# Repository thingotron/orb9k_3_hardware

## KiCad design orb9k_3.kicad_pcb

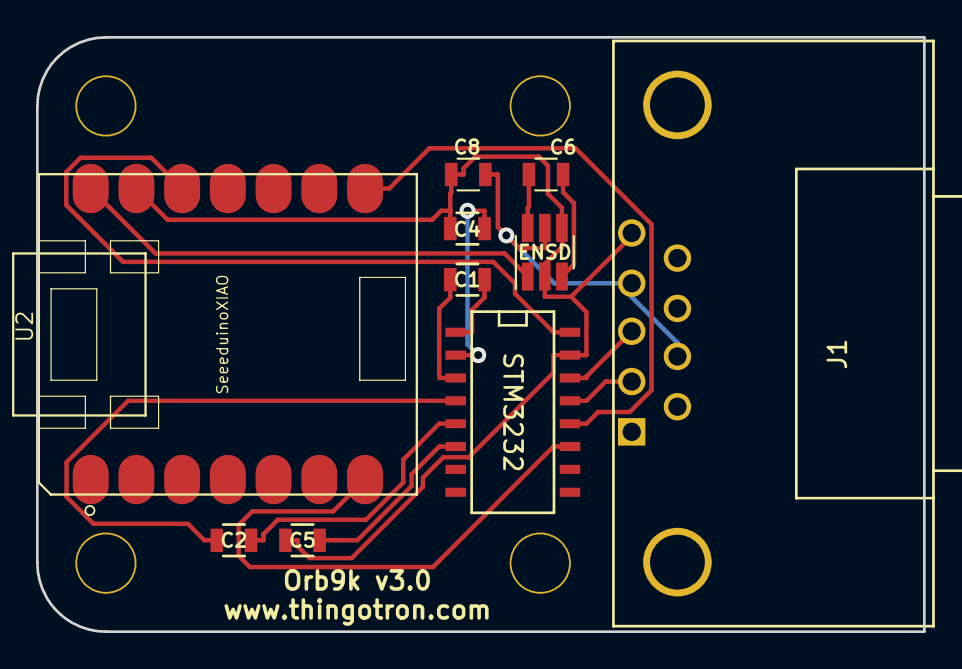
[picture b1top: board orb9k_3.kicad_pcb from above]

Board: 2 copper layers, 49.3 x 33.0 mm, 14 parts (0 on the bottom side), 16 nets.

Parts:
C1, C2, C4, C5: 0.1uf; R_0805
C6, C8: 10uf; R_0805
ENSD: TC1240A; SOT-23-6_Handsoldering
H1, H2, H3, H4: VAL**; M3Hole
J1: DB9-PowerDTRRTS; DB9MC
STM3232: MAX3232; SO-16-N
U2: SeeeduinoXIAO; Seeeduino XIAO-MOUDLE14P-2.54-21X17.8MM

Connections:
+3V3: STM3232.16, U2.12
+10V: C8.1, ENSD.5, J1.4, J1.7
GND: C1.2, C5.1, C8.2, ENSD.2, ENSD.4, J1.5, STM3232.15, U2.13
unnamed: C4.1, STM3232.1
unnamed: C4.2, STM3232.3
unnamed: C2.1, STM3232.4
unnamed: C2.2, STM3232.5
unnamed: C1.1, STM3232.2
unnamed: C5.2, STM3232.6
unnamed: C6.1, ENSD.6
unnamed: C6.2, ENSD.3
unnamed: J1.2, STM3232.13
unnamed: J1.3, STM3232.14
RX0: STM3232.12, U2.8
TX0: STM3232.11, U2.7
VBUS: ENSD.1, U2.14

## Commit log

2016-01-23 initial import
2016-02-08 changes pending for mini-usb
2017-01-02 screwed up prog connect; trying to fix
2017-02-05 first worked, 2/3 inop
2017-04-05 prior to switching serial drivers
2017-05-11 proto1!
2018-09-17 converted schematics to use project lib orb9k_3.lib
2020-01-12 a few changes to catch up
2020-01-19 erased pads from USB
2020-01-19 modified footprint to remove solder pads around USB connector
2020-04-28 changed schema and pcb to use xiao
2020-05-10 Updates to orb9k_3
2021-05-25 added mark's 3d-printed case
